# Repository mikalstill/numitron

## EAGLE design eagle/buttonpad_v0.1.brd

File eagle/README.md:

Breakout versions:

* v0.1: initial version based on a 74LS595
* v0.2: correct labeling of numitron pins, rotate numitron to face flat (I hope)
* v0.3: a higher current shift register
* v0.4: break out debug header into two to provide safer routing, move to a design block for the numitron

Clock versions:

* v0.1: (based on v0.4 breakout)

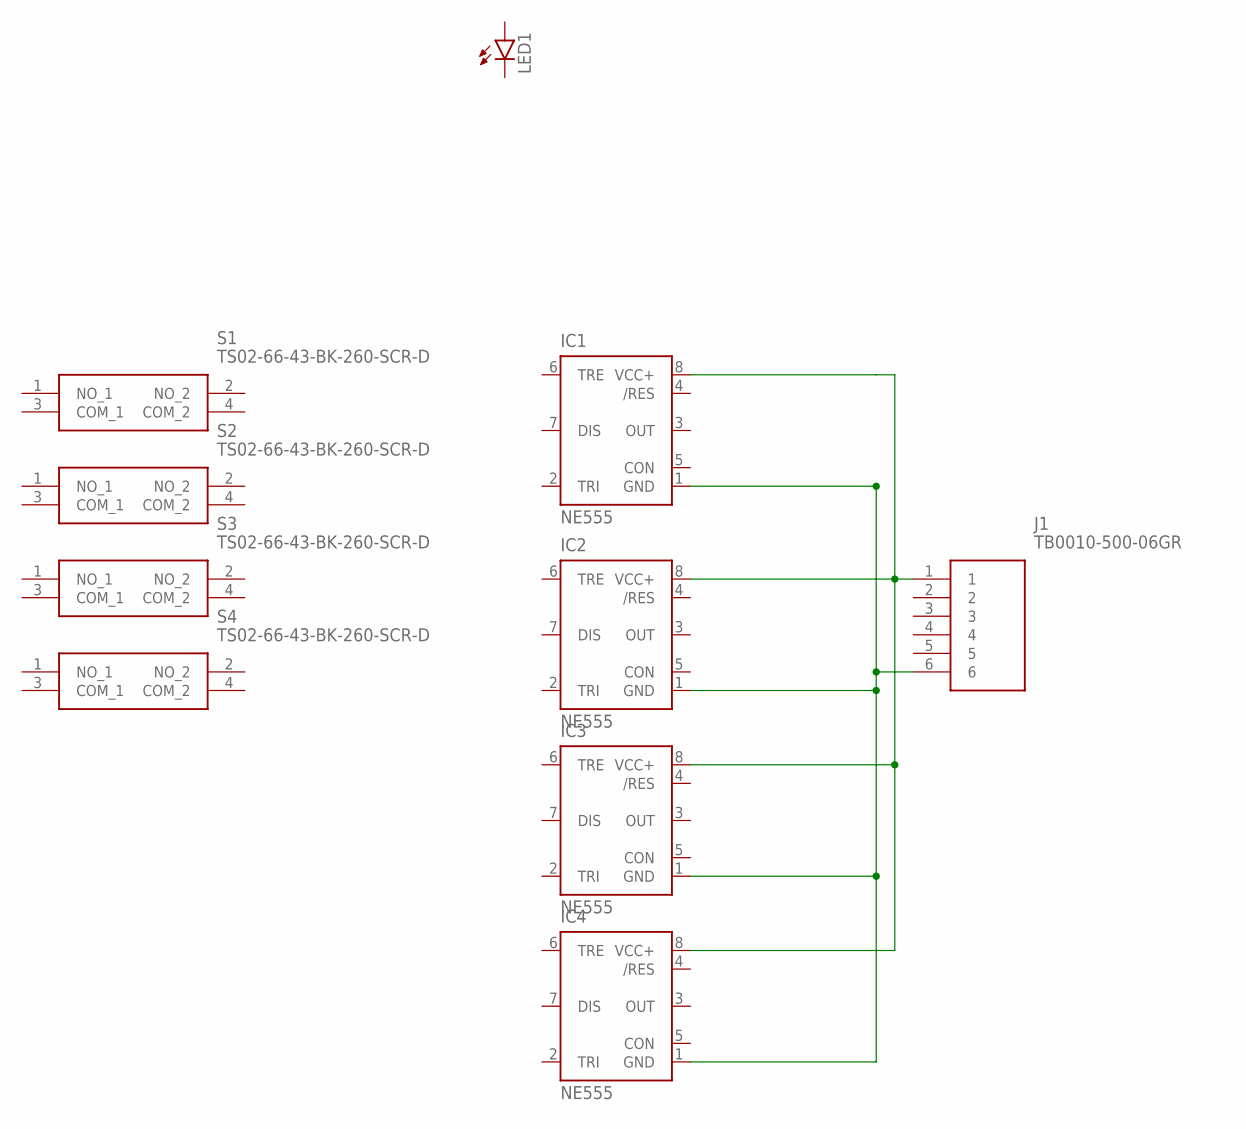
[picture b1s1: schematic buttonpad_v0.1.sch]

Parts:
IC1, IC2, IC3, IC4: NE555; DIL-08
J1: TB0010-500-06GR; TB001050006GR
LED1: LED3MM
S1, S2, S3, S4: TS02-66-43-BK-260-SCR-D; TS026643BK260SCRD

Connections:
unnamed: IC2.8 (VCC+), IC3.8 (VCC+), IC4.8 (VCC+), J1.1
unnamed: IC1.1 (GND), IC2.1 (GND), IC3.1 (GND), IC4.1 (GND), J1.6

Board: 2 copper layers, 10 parts (0 on the bottom side), 2 nets, no tracks yet.

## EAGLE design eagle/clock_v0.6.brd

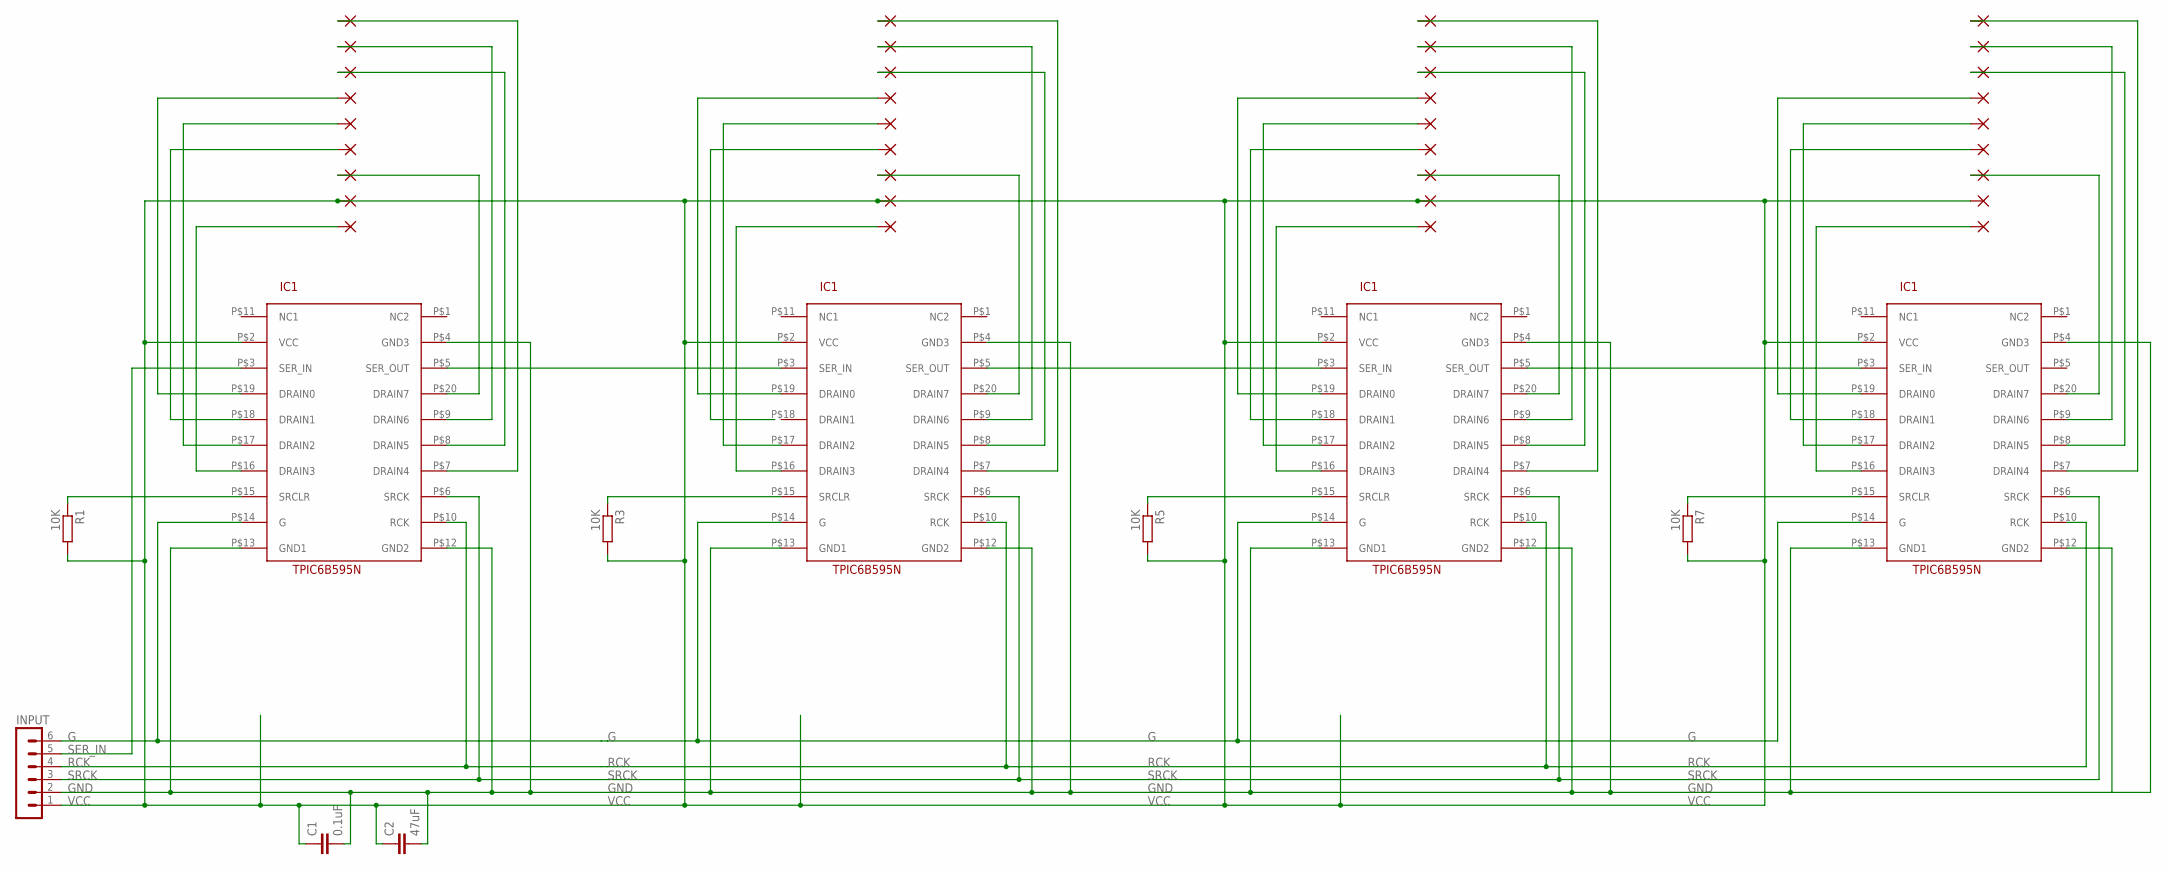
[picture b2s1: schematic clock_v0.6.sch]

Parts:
C1: 0.1uF; RCL_C025-025X050
C2: 47uF; RCL_C025-025X050
DEC1, DEC2, DEC4, DEC6: 1,6/0,8
INPUT: CON-LSTB_MA06-1
R1, R3, R5, R7: 10K; RCL_0207/7
SEGA1, SEGA2, SEGA4, SEGA6: 1,6/0,8
SEGB1, SEGB2, SEGB4, SEGB6: 1,6/0,8
SEGC1, SEGC2, SEGC4, SEGC6: 1,6/0,8
SEGD1, SEGD2, SEGD4, SEGD6: 1,6/0,8
SEGE1, SEGE2, SEGE4, SEGE6: 1,6/0,8
SEGF1, SEGF2, SEGF4, SEGF6: 1,6/0,8
SEGG1, SEGG2, SEGG4, SEGG6: 1,6/0,8
U$1, U$3, U$5, U$7: TPIC6B595N_TPIC6B595NPDIP-20; TPIC6B595N_PDIP-20
VCC1, VCC2, VCC4, VCC6: 1,6/0,8

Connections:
G: INPUT.6, U$1.P$14 (G), U$3.P$14 (G), U$5.P$14 (G), U$7.P$14 (G)
GND: C1.2, C2.2, INPUT.2, U$1.P$4 (GND3), U$1.P$12 (GND2), U$1.P$13 (GND1), U$3.P$4 (GND3), U$3.P$12 (GND2), U$3.P$13 (GND1), U$5.P$4 (GND3), U$5.P$12 (GND2), U$5.P$13 (GND1), U$7.P$4 (GND3), U$7.P$12 (GND2), U$7.P$13 (GND1)
unnamed: R1.1, U$1.P$15 (SRCLR)
unnamed: SEGA1.1, U$1.P$19 (DRAIN0)
unnamed: SEGA2.1, U$3.P$19 (DRAIN0)
unnamed: SEGA4.1, U$5.P$19 (DRAIN0)
unnamed: SEGA6.1, U$7.P$19 (DRAIN0)
unnamed: SEGB1.1, U$1.P$18 (DRAIN1)
unnamed: SEGB4.1, U$5.P$18 (DRAIN1)
unnamed: SEGB6.1, U$7.P$18 (DRAIN1)
unnamed: U$1.P$5 (SER_OUT), U$3.P$3 (SER_IN)
unnamed: U$3.P$5 (SER_OUT), U$5.P$3 (SER_IN)
unnamed: U$5.P$5 (SER_OUT), U$7.P$3 (SER_IN)
unnamed: SEGC1.1, U$1.P$17 (DRAIN2)
unnamed: SEGC2.1, U$3.P$17 (DRAIN2)
unnamed: SEGC4.1, U$5.P$17 (DRAIN2)
unnamed: SEGC6.1, U$7.P$17 (DRAIN2)
unnamed: SEGD1.1, U$1.P$16 (DRAIN3)
unnamed: SEGD2.1, U$3.P$16 (DRAIN3)
unnamed: R3.1, U$3.P$15 (SRCLR)
unnamed: SEGD4.1, U$5.P$16 (DRAIN3)
unnamed: SEGD6.1, U$7.P$16 (DRAIN3)
unnamed: SEGE1.1, U$1.P$7 (DRAIN4)
unnamed: SEGE2.1, U$3.P$7 (DRAIN4)
unnamed: SEGE4.1, U$5.P$7 (DRAIN4)
unnamed: SEGE6.1, U$7.P$7 (DRAIN4)
unnamed: SEGF1.1, U$1.P$8 (DRAIN5)
unnamed: SEGF2.1, U$3.P$8 (DRAIN5)
unnamed: SEGF4.1, U$5.P$8 (DRAIN5)
unnamed: SEGF6.1, U$7.P$8 (DRAIN5)
unnamed: SEGG1.1, U$1.P$9 (DRAIN6)
unnamed: SEGG2.1, U$3.P$9 (DRAIN6)
unnamed: SEGG4.1, U$5.P$9 (DRAIN6)
unnamed: SEGG6.1, U$7.P$9 (DRAIN6)
unnamed: DEC1.1, U$1.P$20 (DRAIN7)
unnamed: DEC2.1, U$3.P$20 (DRAIN7)
unnamed: DEC4.1, U$5.P$20 (DRAIN7)
unnamed: R5.1, U$5.P$15 (SRCLR)
unnamed: DEC6.1, U$7.P$20 (DRAIN7)
unnamed: R7.1, U$7.P$15 (SRCLR)
RCK: INPUT.4, U$1.P$10 (RCK), U$3.P$10 (RCK), U$5.P$10 (RCK), U$7.P$10 (RCK)
SER_IN: INPUT.5, U$1.P$3 (SER_IN)
SRCK: INPUT.3, U$1.P$6 (SRCK), U$3.P$6 (SRCK), U$5.P$6 (SRCK), U$7.P$6 (SRCK)
VCC: C1.1, C2.1, INPUT.1, R1.2, R3.2, R5.2, R7.2, U$1.P$2 (VCC), U$3.P$2 (VCC), U$5.P$2 (VCC), U$7.P$2 (VCC), VCC1.1, VCC2.1, VCC4.1, VCC6.1

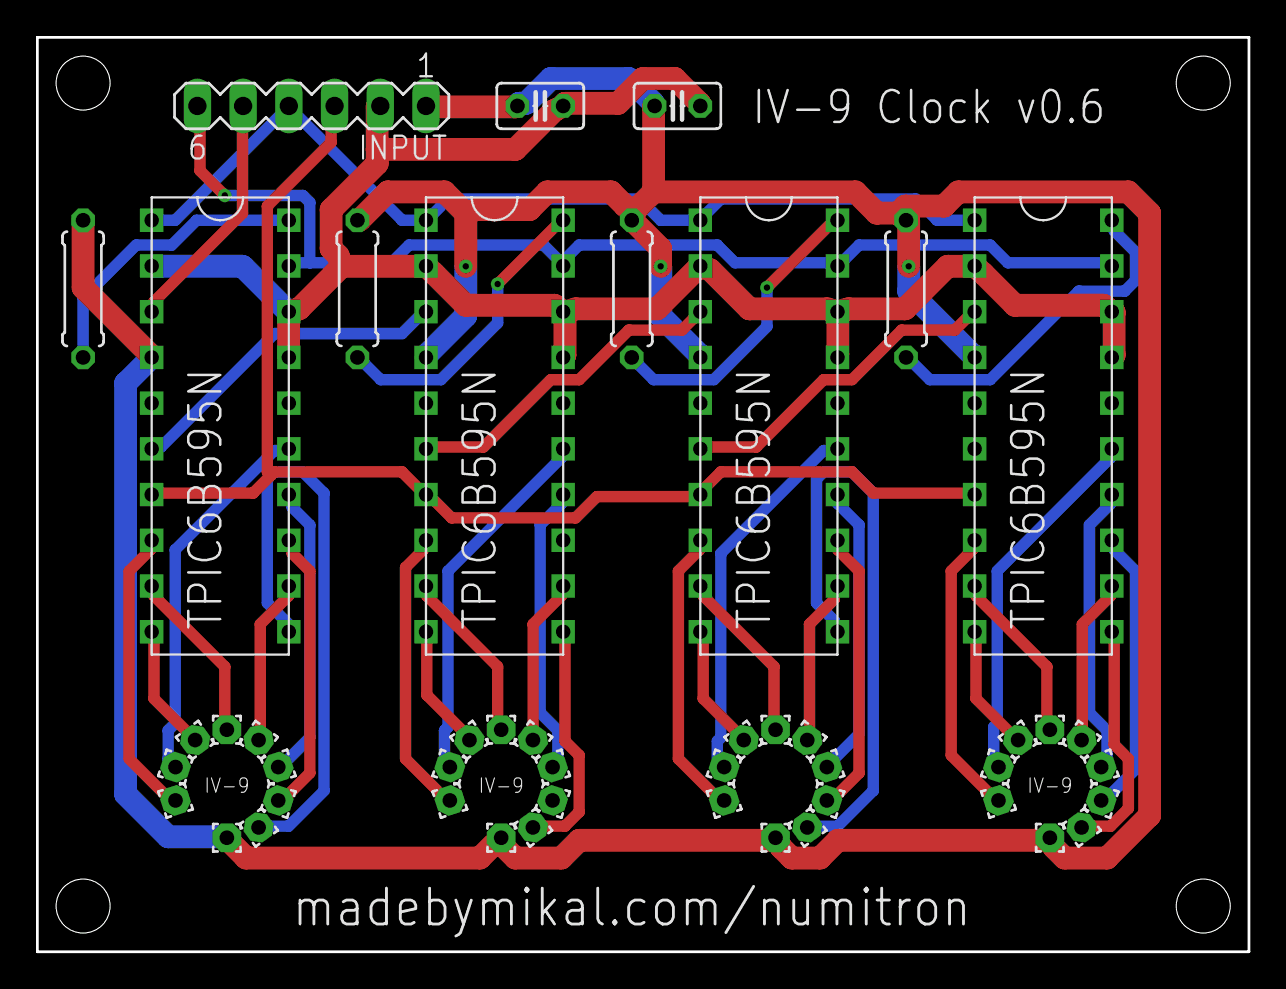
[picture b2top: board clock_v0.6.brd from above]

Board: 2 copper layers, 67.3 x 50.8 mm, 47 parts (0 on the bottom side), 44 nets.

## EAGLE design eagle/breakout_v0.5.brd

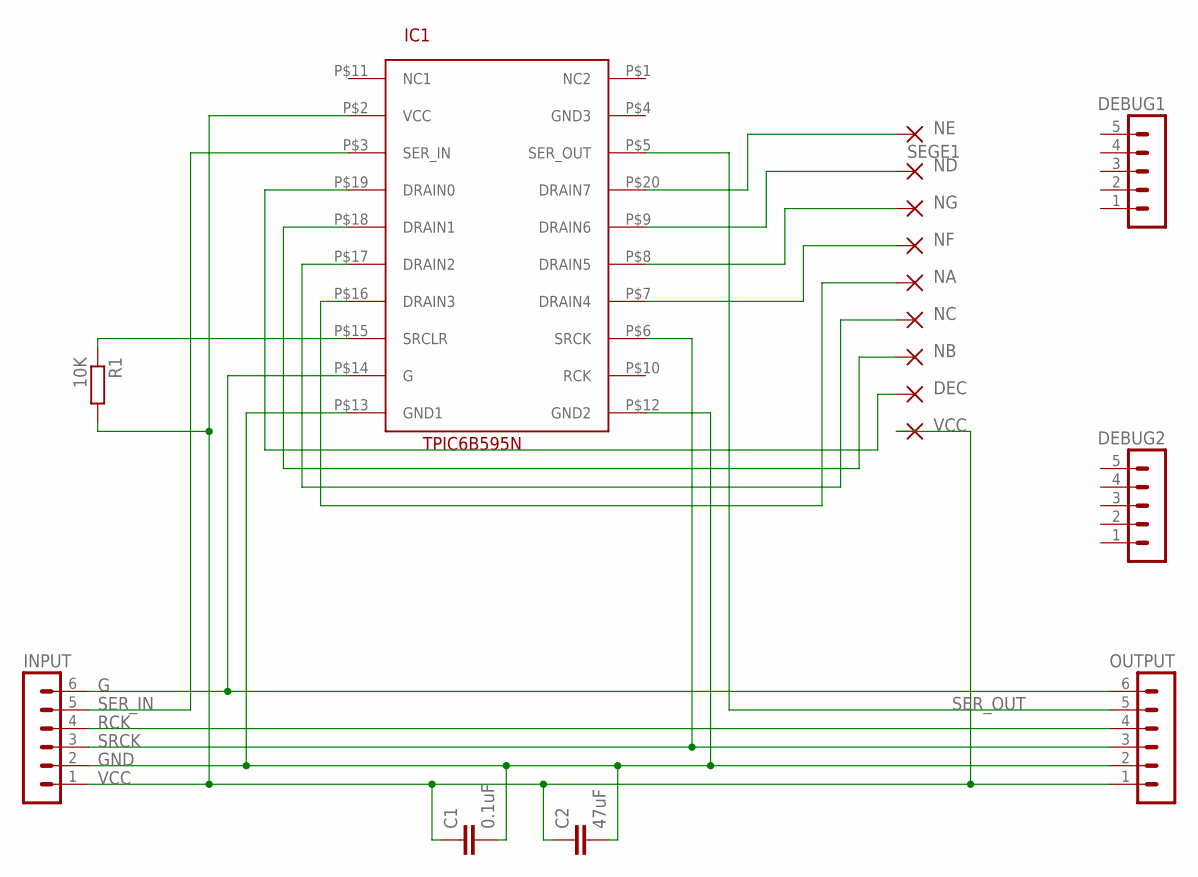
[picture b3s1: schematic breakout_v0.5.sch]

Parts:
C1: 0.1uF; RCL_C025-025X050
C2: 47uF; RCL_C025-025X050
DEBUG1, DEBUG2: MA05-1
DEC1: 1,6/0,8
INPUT: CON-LSTB_MA06-1
OUTPUT: CON-LSTB_MA06-1
R1: 10K; RCL_0207/7
SEGA1: 1,6/0,8
SEGB1: 1,6/0,8
SEGC1: 1,6/0,8
SEGD1: 1,6/0,8
SEGE1: 1,6/0,8
SEGF1: 1,6/0,8
SEGG1: 1,6/0,8
U$1: TPIC6B595N_TPIC6B595NPDIP-20; TPIC6B595N_PDIP-20
VCC1: 1,6/0,8

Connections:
DEC: U$1.P$19 (DRAIN0), VCC1.1
G: INPUT.6, OUTPUT.6, U$1.P$14 (G)
GND: C1.2, C2.2, INPUT.2, OUTPUT.2, U$1.P$12 (GND2), U$1.P$13 (GND1)
unnamed: R1.1, U$1.P$15 (SRCLR)
NA: SEGC1.1, U$1.P$16 (DRAIN3)
NB: DEC1.1, U$1.P$18 (DRAIN1)
NC: SEGB1.1, U$1.P$17 (DRAIN2)
ND: SEGG1.1, U$1.P$9 (DRAIN6)
NE: SEGE1.1, U$1.P$20 (DRAIN7)
NF: SEGA1.1, U$1.P$7 (DRAIN4)
NG: SEGF1.1, U$1.P$8 (DRAIN5)
RCK: INPUT.4, OUTPUT.4
SER_IN: INPUT.5, U$1.P$3 (SER_IN)
SER_OUT: OUTPUT.5, U$1.P$5 (SER_OUT)
SRCK: INPUT.3, OUTPUT.3, U$1.P$6 (SRCK)
VCC: C1.1, C2.1, INPUT.1, OUTPUT.1, R1.2, SEGD1.1, U$1.P$2 (VCC)

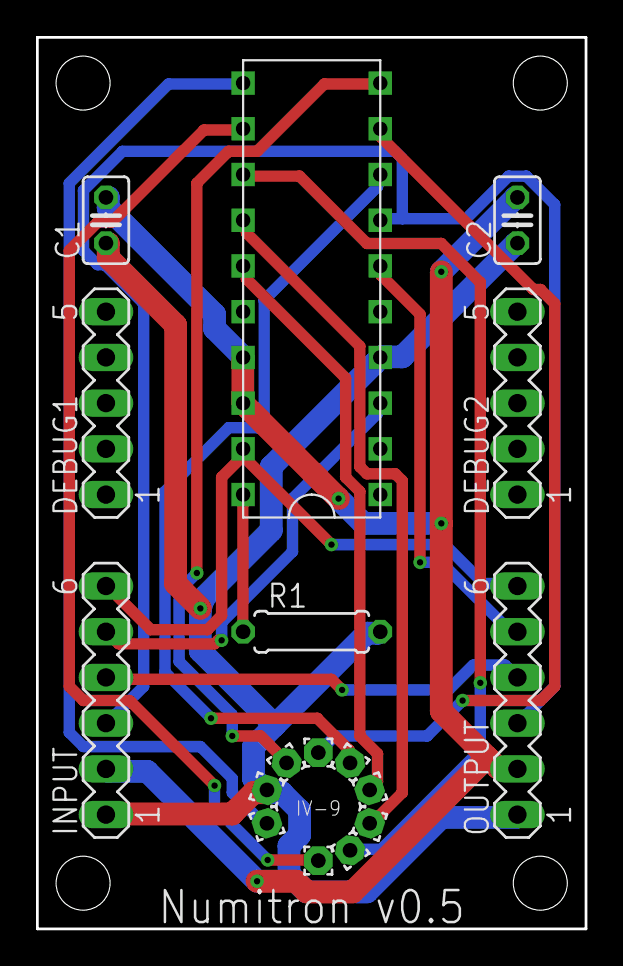
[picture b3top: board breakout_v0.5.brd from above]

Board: 2 copper layers, 30.5 x 49.5 mm, 17 parts (0 on the bottom side), 16 nets.

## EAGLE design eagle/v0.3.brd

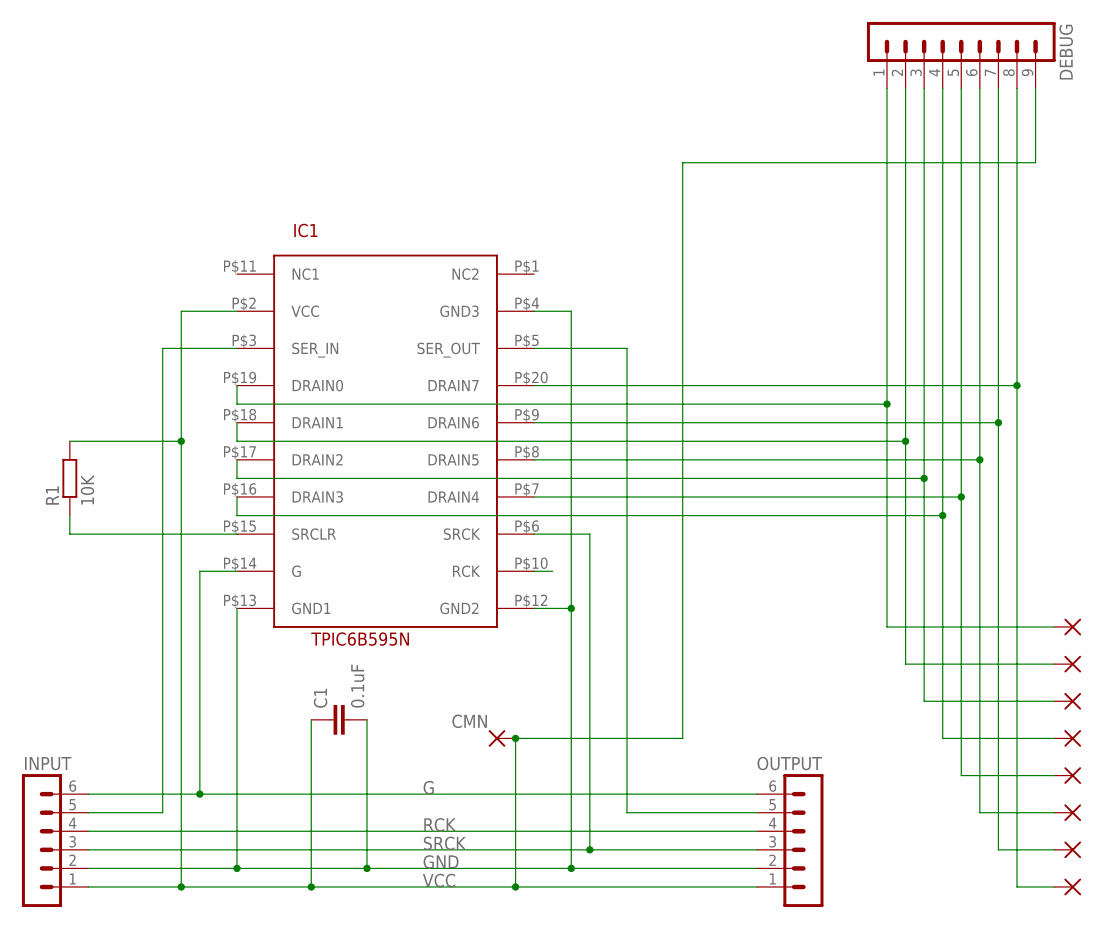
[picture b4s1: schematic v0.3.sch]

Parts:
C1: 0.1uF; C025-025X050
CMN: 1,6/0,8
DEBUG: MA09-1
DEC: 1,6/0,8
INPUT: MA06-1
OUTPUT: MA06-1
R1: 10K; 0207/10
SEGA: 1,6/0,8
SEGB: 1,6/0,8
SEGC: 1,6/0,8
SEGD: 1,6/0,8
SEGE: 1,6/0,8
SEGF: 1,6/0,8
SEGG: 1,6/0,8
U$1: TPIC6B595NPDIP-20; PDIP-20

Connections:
G: INPUT.6, OUTPUT.6, U$1.P$14 (G)
GND: C1.2, INPUT.2, OUTPUT.2, U$1.P$4 (GND3), U$1.P$12 (GND2), U$1.P$13 (GND1); also elsewhere on the board
unnamed: DEBUG.1, SEGA.1, U$1.P$19 (DRAIN0)
unnamed: DEBUG.2, SEGB.1, U$1.P$18 (DRAIN1)
unnamed: DEBUG.3, SEGC.1, U$1.P$17 (DRAIN2)
unnamed: DEBUG.4, SEGD.1, U$1.P$16 (DRAIN3)
unnamed: DEBUG.5, SEGE.1, U$1.P$7 (DRAIN4)
unnamed: DEBUG.6, SEGF.1, U$1.P$8 (DRAIN5)
unnamed: DEBUG.7, SEGG.1, U$1.P$9 (DRAIN6)
unnamed: DEBUG.8, DEC.1, U$1.P$20 (DRAIN7)
unnamed: INPUT.5, U$1.P$3 (SER_IN)
unnamed: OUTPUT.5, U$1.P$5 (SER_OUT)
unnamed: R1.1, U$1.P$15 (SRCLR)
RCK: INPUT.4, OUTPUT.4
SRCK: INPUT.3, OUTPUT.3, U$1.P$6 (SRCK)
VCC: C1.1, CMN.1, DEBUG.9, INPUT.1, OUTPUT.1, R1.2, U$1.P$2 (VCC); also elsewhere on the board

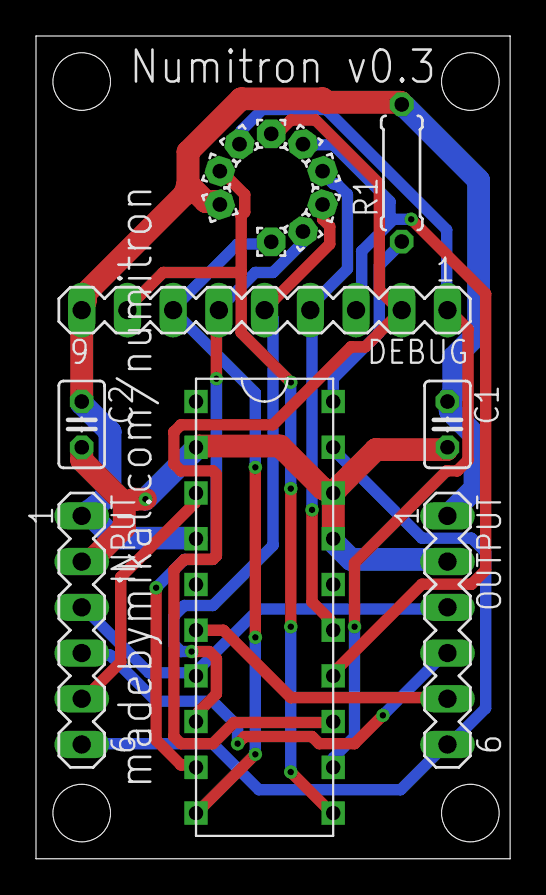
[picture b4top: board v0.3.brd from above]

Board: 2 copper layers, 26.3 x 45.7 mm, 16 parts (0 on the bottom side), 16 nets.

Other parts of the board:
C2: 47uF; C025-025X050

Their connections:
GND: C2.2; also elsewhere on the board
VCC: C2.1; also elsewhere on the board

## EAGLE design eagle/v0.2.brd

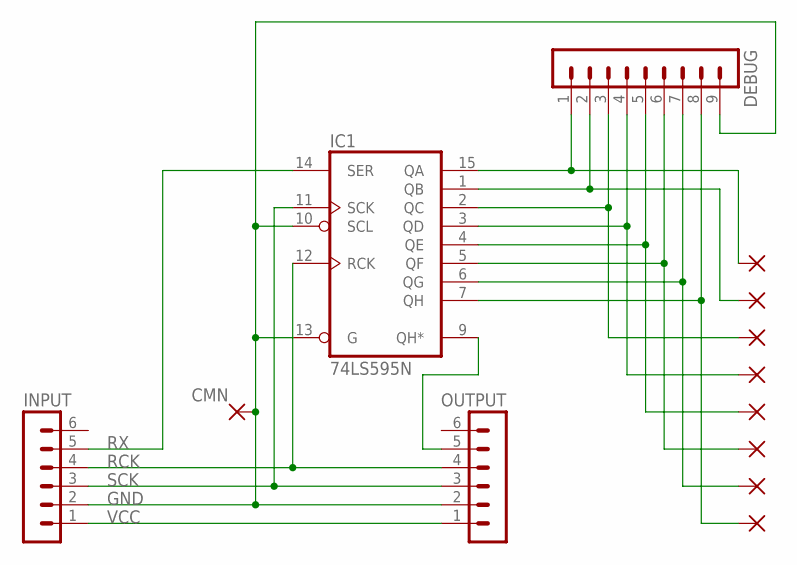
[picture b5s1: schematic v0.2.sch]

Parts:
CMN: 1,6/0,8
DEBUG: MA09-1
DEC: 1,6/0,8
IC1: 74LS595N; DIL16
INPUT: MA06-1
OUTPUT: MA06-1
SEGA: 1,6/0,8
SEGB: 1,6/0,8
SEGC: 1,6/0,8
SEGD: 1,6/0,8
SEGE: 1,6/0,8
SEGF: 1,6/0,8
SEGG: 1,6/0,8

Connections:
GND: CMN.1, DEBUG.9, IC1.8 (GND), IC1.10 (SCL), IC1.13 (G), INPUT.2, OUTPUT.2
unnamed: DEBUG.1, IC1.15 (QA), SEGA.1
unnamed: IC1.9 (QH*), OUTPUT.5
unnamed: DEBUG.3, IC1.2 (QC), SEGC.1
unnamed: DEBUG.4, IC1.3 (QD), SEGD.1
unnamed: DEBUG.5, IC1.4 (QE), SEGE.1
unnamed: DEBUG.6, IC1.5 (QF), SEGF.1
unnamed: DEBUG.7, IC1.6 (QG), SEGG.1
unnamed: DEBUG.8, DEC.1, IC1.7 (QH)
unnamed: DEBUG.2, IC1.1 (QB), SEGB.1
RCK: IC1.12 (RCK), INPUT.4, OUTPUT.4
RX: IC1.14 (SER), INPUT.5
SCK: IC1.11 (SCK), INPUT.3, OUTPUT.3
VCC: IC1.16 (VCC), INPUT.1, OUTPUT.1

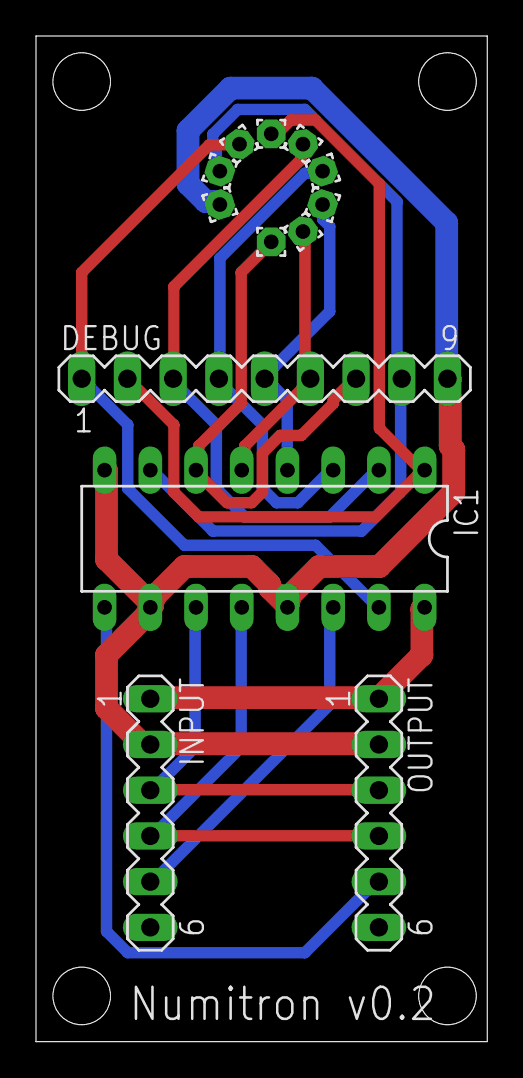
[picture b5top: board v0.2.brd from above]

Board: 2 copper layers, 25.1 x 55.9 mm, 13 parts (0 on the bottom side), 14 nets.

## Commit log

2019-05-20 Initial commit.
2019-05-21 v0.1 as sent to fab
2019-06-04 v0.3 board
2019-06-05 Add another filter cap as recommended by Hugh Blemings.
2019-06-11 Working on a clock version of the breakout board.
2021-02-14 Updated breakout and clock.
    I had the IV-9 socket mirrored from what it should have been.
2024-07-28 New versions of numitron boards.
